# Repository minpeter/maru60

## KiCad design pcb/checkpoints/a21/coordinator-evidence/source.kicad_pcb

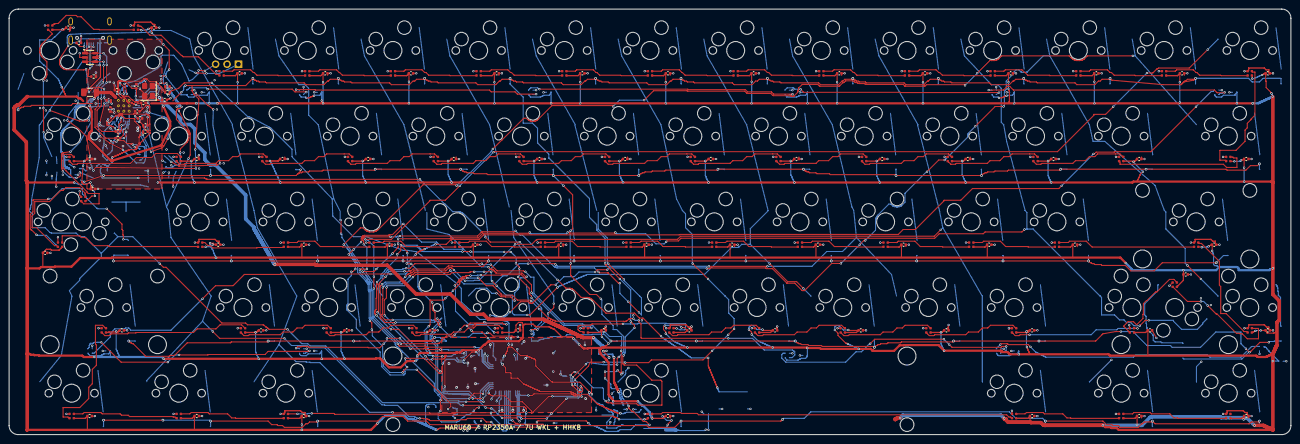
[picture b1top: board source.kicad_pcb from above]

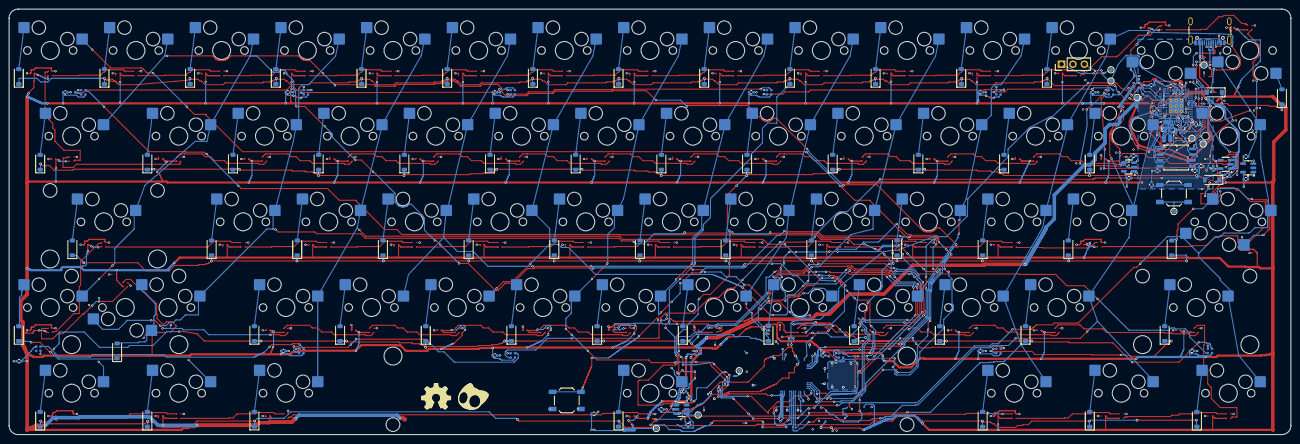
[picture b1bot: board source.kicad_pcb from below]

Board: 4 copper layers, 285.0 x 94.6 mm, 340 parts (192 on the bottom side), 193 nets.

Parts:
C100, C101: 1u 10V; C_0402_1005Metric
C102, C103: 4.7u 6.3V; C_0402_Official_R4_Wide
C104: 4.7u 6.3V; C_0402_1005Metric
C105, C108, C110, C111, C112, C113, C114, C115, C116, C117, C118, C122, C123, C199: 100n; C_0402_1005Metric
C106, C107: 15p C0G; C_0402_1005Metric
C109: 4.7u 6.3V X5R; C_0402_1005Metric
C120: 1u; C_0402_1005Metric
C121: 4.7u; C_0402_1005Metric
C200, C201, C202, C203, C204, C205, C206, C207, C208, C209, C210, C211, C212, C213, C214, C215, C216, C217, C218, C219, C220, C221, C222, C223, C224, C225, C226, C227, C228, C229, C230, C231, C232, C233, C234, C235, C236, C237, C238, C239, C240, C241, C242, C243, C244, C245, C246, C247, C248, C249, C250, C251, C252, C253, C254, C255, C256, C257, C258, C259, C260, C261, C262, C263, C264, C265, C266, C267, C268, C269, C270, C271, C272, C273: 100nF; C_0402_1005Metric
C274, C275: 100nF 10V X7R candidate; C_0402_1005Metric
D1, D2, D3, D4, D5, D6, D7, D8, D9, D10, D11, D12, D13, D14, D15, D16, D17, D18, D19, D20, D21, D22, D23, D24, D25, D26, D27, D28, D29, D30, D31, D32, D33, D34, D35, D36, D37, D38, D39, D40, D41, D42, D43, D44, D45, D46, D47, D48, D49, D50, D51, D52, D53, D54, D55, D56, D57, D58, D59, D60, D61, D62: 1N4148W; D_SOD-123
F1: 500mA hold candidate; Fuse_1206_3216Metric
J1: USB4105-GF-A (candidate); USB_C_Receptacle_GCT_USB4105-xx-A_16P_TopMnt_Horizontal
J2: SWD / GND / SWCLK; PinHeader_1x03_P2.54mm_Vertical
L1: 3.3uH AOTA-B201610S3R3-101-T; Abracon_AOTA_B201610S3R3_Official_R4
LED1, LED2, LED3, LED4, LED5, LED6, LED7, LED8, LED9, LED10, LED11, LED12, LED13, LED14, LED15, LED16, LED17, LED18, LED19, LED20, LED21, LED22, LED23, LED24, LED25, LED26, LED27, LED28, LED29, LED30, LED31, LED32, LED33, LED34, LED35, LED36, LED37, LED38, LED39, LED40, LED41, LED42, LED43, LED44, LED45, LED46, LED47, LED48, LED49, LED50, LED51, LED52, LED53, LED54, LED55, LED56, LED57, LED58, LED59, LED60, LED61, LED62, LED63, LED64, LED65, LED66, LED67, LED68, LED69, LED70, LED71, LED72, LED73, LED74, LED75, LED76: SK6805-EC15-001; LED_SK6805_EC15_001_Recommended_Candidate
LOGO1: OSHW + minpeter character — DRAFT; OSHW_then_Minpeter_H6_Gap1p5_Silk_DRAFT
R100, R101: 5.1k 1%; R_0402_1005Metric
R102, R103: 27; R_0402_1005Metric
R104: 33; R_0402_1005Metric
R105, R113, R114: 10k; R_0402_1005Metric
R106, R107, R108: 1k; R_0402_1005Metric
R109: 100k; R_0402_1005Metric
R110, R111: 330; R_0402_1005Metric
R112: 133k 1%; R_0402_1005Metric
STAB_RS1: (no value)
SW1: Esc; MX-Hotswap-1U
SW2: 1; MX-Hotswap-1U
SW3: 2; MX-Hotswap-1U
SW4: 3; MX-Hotswap-1U
SW5: 4; MX-Hotswap-1U
SW6: 5; MX-Hotswap-1U
SW7: 6; MX-Hotswap-1U
SW8: 7; MX-Hotswap-1U
SW9: 8; MX-Hotswap-1U
SW10: 9; MX-Hotswap-1U
SW11: 0; MX-Hotswap-1U
SW12: Minus; MX-Hotswap-1U
SW13: Equal; MX-Hotswap-1U
SW14: Backspace_L; MX-Hotswap-1U
SW15: Backspace_R; MX-Hotswap-1U
SW16: Tab; MX-Hotswap-1U
SW17: Q; MX-Hotswap-1U
SW18: W; MX-Hotswap-1U
SW19: E; MX-Hotswap-1U
SW20: R; MX-Hotswap-1U
SW21: T; MX-Hotswap-1U
SW22: Y; MX-Hotswap-1U
SW23: U; MX-Hotswap-1U
SW24: I; MX-Hotswap-1U
SW25: O; MX-Hotswap-1U
SW26: P; MX-Hotswap-1U
SW27: LeftBracket; MX-Hotswap-1U
SW28: RightBracket; MX-Hotswap-1U
SW29: Backslash; MX-Hotswap-1U
SW31: A; MX-Hotswap-1U
SW32: S; MX-Hotswap-1U
SW33: D; MX-Hotswap-1U
SW34: F; MX-Hotswap-1U
SW35: G; MX-Hotswap-1U
SW36: H; MX-Hotswap-1U
SW37: J; MX-Hotswap-1U
SW38: K; MX-Hotswap-1U
SW39: L; MX-Hotswap-1U
SW40: Semicolon; MX-Hotswap-1U
SW41: Quote; MX-Hotswap-1U
SW42: Enter; MX-Hotswap-2.25U-4L-NPTH
SW43: LeftShift; MX-Hotswap-2.25U-4L-NPTH
SW44: Z; MX-Hotswap-1U
SW45: X; MX-Hotswap-1U
SW46: C; MX-Hotswap-1U
SW47: V; MX-Hotswap-1U
SW48: B; MX-Hotswap-1U
SW49: N; MX-Hotswap-1U
SW50: M; MX-Hotswap-1U
SW51: Comma; MX-Hotswap-1U
SW52: Period; MX-Hotswap-1U
SW53: Slash; MX-Hotswap-1U
SW56: LCtrl; MX-Hotswap-1U
SW57: LMeta; MX-Hotswap-1U
SW58: LAlt; MX-Hotswap-1U
SW59: Space; MX-Hotswap-7U-4L-NPTH-StabRot180
SW60: RAlt; MX-Hotswap-1U
SW61: RMeta; MX-Hotswap-1U
SW62: RCtrl; MX-Hotswap-1U
SW100: BOOTSEL; SW_SPST_TL3342
SW101: RESET; SW_SPST_TL3342
SWCAP1: Caps_Options; MX_Study_Caps_Normal_or_Stepped
SWRS1: RShift_Options; MX_Study_RShift_2.75U_or_1.75U_1U
TP1: GND TEST; TestPoint_Pad_D1.0mm
TP2: VBUS TEST; TestPoint_Pad_D1.0mm
TP3: +5V TEST; TestPoint_Pad_D1.0mm
TP4: +3V3 TEST; TestPoint_Pad_D1.0mm
TP5: +1V1 TEST; TestPoint_Pad_D1.0mm
TP6: RUN TEST; TestPoint_Pad_D1.0mm
TP7: SWDIO TEST; TestPoint_Pad_D1.0mm
TP8: SWCLK TEST; TestPoint_Pad_D1.0mm
TP9: LED_FAULT_N TEST; TestPoint_Pad_D1.0mm
TP10: +5V_LED TEST; TestPoint_Pad_D1.0mm
U1: RP2350A (A4 required); RP2350A_QFN60_Official_R4
U2: AP2112K-3.3TRG1; SOT-23-5
U3: W25Q32JVSSIQ (4MiB); SOIC-8_5.3x5.3mm_P1.27mm
U4: USBLC6-2SC6; SOT-23-6
U5, U6: SN74LV1T125DBVR; SOT-23-5
U7: TPS2553DBVR-1; SOT-23-6
Y1: 12MHz ABM8-272-T3; Crystal_SMD_3225-4Pin_3.2x2.5mm

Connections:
+1V1: C103.1, C108.1, C109.1, C110.1, L1.1, TP5.1, U1.6, U1.23, U1.39, U1.50
+3V3: C101.1, C102.1, C105.1, C111.1, C112.1, C113.1, C114.1, C115.1, C116.1, C117.1, C118.1, C199.1, R104.1, R105.1, R113.1, TP4.1, U1.1, U1.11, U1.20, U1.30, U1.38, U1.44, U1.45, U1.49, U1.53, U1.54, U2.5, U3.8
+5V: C100.1, C120.1, F1.2, TP3.1, U2.1, U2.3, U7.1
+5V_LED: C121.1, C122.1, C123.1, C200.1, C201.1, C202.1, C203.1, C204.1, C205.1, C206.1, C207.1, C208.1, C209.1, C210.1, C211.1, C212.1, C213.1, C214.1, C215.1, C216.1, C217.1, C218.1, C219.1, C220.1, C221.1, C222.1, C223.1, C224.1, C225.1, C226.1, C227.1, C228.1, C229.1, C230.1, C231.1, C232.1, C233.1, C234.1, C235.1, C236.1, C237.1, C238.1, C239.1, C240.1, C241.1, C242.1, C243.1, C244.1, C245.1, C246.1, C247.1, C248.1, C249.1, C250.1, C251.1, C252.1, C253.1, C254.1, C255.1, C256.1, C257.1, C258.1, C259.1, C260.1, C261.1, C262.1, C263.1, C264.1, C265.1, C266.1, C267.1, C268.1, C269.1, C270.1, C271.1, C272.1, C273.1, C274.1, C275.1, LED1.2, LED2.2, LED3.2, LED4.2, LED5.2, LED6.2, LED7.2, LED8.2, LED9.2, LED10.2, LED11.2, LED12.2, LED13.2, LED14.2, LED15.2, LED16.2, LED17.2, LED18.2, LED19.2, LED20.2, LED21.2, LED22.2, LED23.2, LED24.2, LED25.2, LED26.2, LED27.2, LED28.2, LED29.2, LED30.2, LED31.2, LED32.2, LED33.2, LED34.2, LED35.2, LED36.2, LED37.2, LED38.2, LED39.2, LED40.2, LED41.2, LED42.2, LED43.2, LED44.2, LED45.2, LED46.2, LED47.2, LED48.2, LED49.2, LED50.2, LED51.2, LED52.2, LED53.2, LED54.2, LED55.2, LED56.2, LED57.2, LED58.2, LED59.2, LED60.2, LED61.2, LED62.2, LED63.2, LED64.2, LED65.2, LED66.2, LED67.2, LED68.2, LED69.2, LED70.2, LED71.2, LED72.2, LED73.2, LED74.2, LED75.2, LED76.2, R114.1, TP10.1, U5.5, U6.5, U7.6
BOOT_BUTTON: R106.2, SW100.1
CC1: J1.A5, R100.1
CC2: J1.B5, R101.1
COL0: SW1.1, SW16.1, SW43.1, SW56.1, SWCAP1.1, SWCAP1.3, U1.8
COL1: SW2.1, SW17.1, SW31.1, SW44.1, SW57.1, U1.9
COL2: SW3.1, SW18.1, SW32.1, SW45.1, SW58.1, U1.10
COL3: SW4.1, SW19.1, SW33.1, SW46.1, U1.12
COL4: SW5.1, SW20.1, SW34.1, SW47.1, U1.13
COL5: SW6.1, SW21.1, SW35.1, SW48.1, U1.42
COL6: SW7.1, SW22.1, SW36.1, SW49.1, SW59.1, U1.15
COL7: SW8.1, SW23.1, SW37.1, SW50.1, U1.16
COL8: SW9.1, SW24.1, SW38.1, SW51.1, U1.17
COL9: SW10.1, SW25.1, SW39.1, SW52.1, U1.18
COL10: SW11.1, SW26.1, SW40.1, SW53.1, SW60.1, U1.19
COL11: SW12.1, SW27.1, SW41.1, SW61.1, SWRS1.1, SWRS1.3, U1.27
COL12: SW13.1, SW28.1, SW42.1, SW62.1, SWRS1.5, U1.28
COL13: SW14.1, SW29.1, U1.29
COL14: SW15.1, U1.31
GND: C100.2, C101.2, C102.2, C103.2, C104.2, C105.2, C106.2, C107.2, C108.2, C109.2, C110.2, C111.2, C112.2, C113.2, C114.2, C115.2, C116.2, C117.2, C118.2, C120.2, C121.2, C122.2, C123.2, C199.2, C200.2, C201.2, C202.2, C203.2, C204.2, C205.2, C206.2, C207.2, C208.2, C209.2, C210.2, C211.2, C212.2, C213.2, C214.2, C215.2, C216.2, C217.2, C218.2, C219.2, C220.2, C221.2, C222.2, C223.2, C224.2, C225.2, C226.2, C227.2, C228.2, C229.2, C230.2, C231.2, C232.2, C233.2, C234.2, C235.2, C236.2, C237.2, C238.2, C239.2, C240.2, C241.2, C242.2, C243.2, C244.2, C245.2, C246.2, C247.2, C248.2, C249.2, C250.2, C251.2, C252.2, C253.2, C254.2, C255.2, C256.2, C257.2, C258.2, C259.2, C260.2, C261.2, C262.2, C263.2, C264.2, C265.2, C266.2, C267.2, C268.2, C269.2, C270.2, C271.2, C272.2, C273.2, C274.2, C275.2, J1.A1, J1.A12, J1.B1, J1.B12, J1.S1, J2.2, LED1.4, LED2.4, LED3.4, LED4.4, LED5.4, LED6.4, LED7.4, LED8.4, LED9.4, LED10.4, LED11.4, LED12.4, LED13.4, LED14.4, LED15.4, LED16.4, LED17.4, LED18.4, LED19.4, LED20.4, LED21.4, LED22.4, LED23.4, LED24.4, LED25.4, LED26.4, LED27.4, LED28.4, LED29.4, LED30.4, LED31.4, LED32.4, LED33.4, LED34.4, LED35.4, LED36.4, LED37.4, LED38.4, LED39.4, LED40.4, LED41.4, LED42.4, LED43.4, LED44.4, LED45.4, LED46.4, LED47.4, LED48.4, LED49.4, LED50.4, LED51.4, LED52.4, LED53.4, LED54.4, LED55.4, LED56.4, LED57.4, LED58.4, LED59.4, LED60.4, LED61.4, LED62.4, LED63.4, LED64.4, LED65.4, LED66.4, LED67.4, LED68.4, LED69.4, LED70.4, LED71.4, LED72.4, LED73.4, LED74.4, LED75.4, LED76.4, R100.2, R101.2, R107.2, R109.2, R112.2, R114.2, SW100.2, TP1.1, U1.47, U1.61, U2.2, U3.4, U4.2, U5.1, U5.3, U6.1, U6.3, U7.2, Y1.2, Y1.4
KEY_1: D1.2, SW1.2
KEY_2: D2.2, SW2.2
KEY_3: D3.2, SW3.2
KEY_4: D4.2, SW4.2
KEY_5: D5.2, SW5.2
KEY_6: D6.2, SW6.2
KEY_7: D7.2, SW7.2
KEY_8: D8.2, SW8.2
KEY_9: D9.2, SW9.2
KEY_10: D10.2, SW10.2
KEY_11: D11.2, SW11.2
KEY_12: D12.2, SW12.2
KEY_13: D13.2, SW13.2
KEY_14: D14.2, SW14.2
KEY_15: D15.2, SW15.2
KEY_16: D16.2, SW16.2
KEY_17: D17.2, SW17.2
KEY_18: D18.2, SW18.2
KEY_19: D19.2, SW19.2
KEY_20: D20.2, SW20.2
KEY_21: D21.2, SW21.2
KEY_22: D22.2, SW22.2
KEY_23: D23.2, SW23.2
KEY_24: D24.2, SW24.2
KEY_25: D25.2, SW25.2
KEY_26: D26.2, SW26.2
KEY_27: D27.2, SW27.2
KEY_28: D28.2, SW28.2
KEY_29: D29.2, SW29.2
KEY_30: D30.2, SWCAP1.2, SWCAP1.4
KEY_31: D31.2, SW31.2
KEY_32: D32.2, SW32.2
KEY_33: D33.2, SW33.2
KEY_34: D34.2, SW34.2
KEY_35: D35.2, SW35.2
KEY_36: D36.2, SW36.2
KEY_37: D37.2, SW37.2
KEY_38: D38.2, SW38.2
KEY_39: D39.2, SW39.2
KEY_40: D40.2, SW40.2
KEY_41: D41.2, SW41.2
KEY_42: D42.2, SW42.2
KEY_43: D43.2, SW43.2
KEY_44: D44.2, SW44.2
KEY_45: D45.2, SW45.2
KEY_46: D46.2, SW46.2
KEY_47: D47.2, SW47.2
KEY_48: D48.2, SW48.2
KEY_49: D49.2, SW49.2
KEY_50: D50.2, SW50.2
KEY_51: D51.2, SW51.2
KEY_52: D52.2, SW52.2
KEY_53: D53.2, SW53.2
KEY_54: D54.2, SWRS1.2, SWRS1.4
KEY_55: D55.2, SWRS1.6
KEY_56: D56.2, SW56.2
KEY_57: D57.2, SW57.2
KEY_58: D58.2, SW58.2
KEY_59: D59.2, SW59.2
KEY_60: D60.2, SW60.2
KEY_61: D61.2, SW61.2
KEY_62: D62.2, SW62.2
KEY_RGB: U1.32, U5.2
KEY_RGB_5V: LED1.1, R110.2
KEY_RGB_5V_BUF: R110.1, U5.4
KEY_RGB_CHAIN_1: LED1.3, LED2.1
KEY_RGB_CHAIN_2: LED2.3, LED3.1
KEY_RGB_CHAIN_3: LED3.3, LED4.1
KEY_RGB_CHAIN_4: LED4.3, LED5.1
KEY_RGB_CHAIN_5: LED5.3, LED6.1
KEY_RGB_CHAIN_6: LED6.3, LED7.1
KEY_RGB_CHAIN_7: LED7.3, LED8.1
KEY_RGB_CHAIN_8: LED8.3, LED9.1
KEY_RGB_CHAIN_9: LED9.3, LED10.1
KEY_RGB_CHAIN_10: LED10.3, LED11.1
KEY_RGB_CHAIN_11: LED11.3, LED12.1
KEY_RGB_CHAIN_12: LED12.3, LED13.1
KEY_RGB_CHAIN_13: LED13.3, LED14.1
KEY_RGB_CHAIN_14: LED14.3, LED15.1
KEY_RGB_CHAIN_15: LED15.3, LED29.1
KEY_RGB_CHAIN_16: LED28.1, LED29.3
KEY_RGB_CHAIN_17: LED27.1, LED28.3
KEY_RGB_CHAIN_18: LED26.1, LED27.3
KEY_RGB_CHAIN_19: LED25.1, LED26.3
KEY_RGB_CHAIN_20: LED24.1, LED25.3
KEY_RGB_CHAIN_21: LED23.1, LED24.3
KEY_RGB_CHAIN_22: LED22.1, LED23.3
KEY_RGB_CHAIN_23: LED21.1, LED22.3
KEY_RGB_CHAIN_24: LED20.1, LED21.3
KEY_RGB_CHAIN_25: LED19.1, LED20.3
KEY_RGB_CHAIN_26: LED18.1, LED19.3
KEY_RGB_CHAIN_27: LED17.1, LED18.3
KEY_RGB_CHAIN_28: LED16.1, LED17.3
KEY_RGB_CHAIN_29: LED16.3, LED30.1
KEY_RGB_CHAIN_30: LED30.3, LED75.1
KEY_RGB_CHAIN_31: LED31.1, LED75.3
KEY_RGB_CHAIN_32: LED31.3, LED32.1
KEY_RGB_CHAIN_33: LED32.3, LED33.1
KEY_RGB_CHAIN_34: LED33.3, LED34.1
KEY_RGB_CHAIN_35: LED34.3, LED35.1
KEY_RGB_CHAIN_36: LED35.3, LED36.1
KEY_RGB_CHAIN_37: LED36.3, LED37.1
KEY_RGB_CHAIN_38: LED37.3, LED38.1
KEY_RGB_CHAIN_39: LED38.3, LED39.1
KEY_RGB_CHAIN_40: LED39.3, LED40.1
KEY_RGB_CHAIN_41: LED40.3, LED41.1
KEY_RGB_CHAIN_42: LED41.3, LED42.1
KEY_RGB_CHAIN_43: LED42.3, LED55.1
KEY_RGB_CHAIN_44: LED55.3, LED76.1
KEY_RGB_CHAIN_45: LED54.1, LED76.3
KEY_RGB_CHAIN_46: LED53.1, LED54.3
KEY_RGB_CHAIN_47: LED52.1, LED53.3
KEY_RGB_CHAIN_48: LED51.1, LED52.3
KEY_RGB_CHAIN_49: LED50.1, LED51.3
KEY_RGB_CHAIN_50: LED49.1, LED50.3
KEY_RGB_CHAIN_51: LED48.1, LED49.3
KEY_RGB_CHAIN_52: LED47.1, LED48.3
KEY_RGB_CHAIN_53: LED46.1, LED47.3
KEY_RGB_CHAIN_54: LED45.1, LED46.3
KEY_RGB_CHAIN_55: LED44.1, LED45.3
KEY_RGB_CHAIN_56: LED43.1, LED44.3
KEY_RGB_CHAIN_57: LED43.3, LED56.1
KEY_RGB_CHAIN_58: LED56.3, LED57.1
KEY_RGB_CHAIN_59: LED57.3, LED58.1
KEY_RGB_CHAIN_60: LED58.3, LED59.1
KEY_RGB_CHAIN_61: LED59.3, LED60.1
KEY_RGB_CHAIN_62: LED60.3, LED61.1
KEY_RGB_CHAIN_63: LED61.3, LED62.1
LED_ENABLE: R109.1, U1.34, U7.3
LED_FAULT_N: R113.2, TP9.1, U1.35, U7.4
LED_ILIM: R112.1, U7.5
QSPI_SCLK: U1.56, U3.6
QSPI_SD0: U1.57, U3.5
QSPI_SD1: U1.59, U3.2
QSPI_SD2: U1.58, U3.3
QSPI_SD3: U1.55, U3.7
QSPI_SS: R105.2, R106.1, U1.60, U3.1
RESET_GND: R107.1, SW101.2
ROW0: D1.1, D2.1, D3.1, D4.1, D5.1, D6.1, D7.1, D8.1, D9.1, D10.1, D11.1, D12.1, D13.1, D14.1, D15.1, U1.2
ROW1: D16.1, D17.1, D18.1, D19.1, D20.1, D21.1, D22.1, D23.1, D24.1, D25.1, D26.1, D27.1, D28.1, D29.1, U1.3
ROW2: D30.1, D31.1, D32.1, D33.1, D34.1, D35.1, D36.1, D37.1, D38.1, D39.1, D40.1, D41.1, D42.1, U1.4
ROW3: D43.1, D44.1, D45.1, D46.1, D47.1, D48.1, D49.1, D50.1, D51.1, D52.1, D53.1, D54.1, D55.1, U1.43
ROW4: D56.1, D57.1, D58.1, D59.1, D60.1, D61.1, D62.1, U1.7
RUN: SW101.1, TP6.1, U1.26
SWCLK: J2.3, TP8.1, U1.24
SWDIO: J2.1, TP7.1, U1.25
UG_LED_1: LED63.3, LED64.1
UG_LED_2: LED64.3, LED65.1
UG_LED_3: LED65.3, LED66.1
UG_LED_4: LED66.3, LED67.1
UG_LED_5: LED67.3, LED68.1
UG_LED_6: LED68.3, LED69.1
UG_LED_7: LED69.3, LED70.1
UG_LED_8: LED70.3, LED71.1
UG_LED_9: LED71.3, LED72.1
UG_LED_10: LED72.3, LED73.1
UG_LED_11: LED73.3, LED74.1
UNDERGLOW: U1.33, U6.2
UNDERGLOW_5V: LED63.1, R111.2
UNDERGLOW_5V_BUF: R111.1, U6.4
USB_DM: R103.2, U1.51
USB_DM_CONN: J1.A7, J1.B7, R103.1, U4.3, U4.4
USB_DP: R102.2, U1.52
USB_DP_CONN: J1.A6, J1.B6, R102.1, U4.1, U4.6
VBUS: F1.1, J1.A4, J1.A9, J1.B4, J1.B9, TP2.1, U4.5
VREG_AVDD: C104.1, R104.2, U1.46
VREG_LX: L1.2, U1.48
XIN: C106.1, U1.21, Y1.1
XOUT: R108.2, U1.22
XTAL_OUT: C107.1, R108.1, Y1.3

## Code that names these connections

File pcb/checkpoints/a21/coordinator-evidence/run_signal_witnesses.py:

from pathlib import Path
import json,hashlib,subprocess,os
D=Path(__file__).parent;O=D/'signal-source-gates';O.mkdir(exist_ok=False);B=D/'candidate.kicad_pcb';C=Path('/workspace/shared/maru60-kicad-linux/pcb/tools/studies/experiment_a_power_witness.py');sha=lambda p:hashlib.sha256(p.read_bytes()).hexdigest();inputs=[B,B.with_suffix('.kicad_pro'),C];base={str(p):sha(p)for p in inputs};rows=[];env=os.environ.copy();env['KICAD_CONFIG_HOME']='/tmp/maru-kicad-config'
for name,net,ref,pin in [('XIN','XIN','U1','21'),('XOUT','XOUT','U1','22'),('XTAL','XTAL_OUT','R108','1'),('UNDERGLOW','UNDERGLOW','U1','33'),('FAULT','LED_FAULT_N','U7','4'),('ENABLE','LED_ENABLE','U1','34'),('COL1','COL1','U1','9')]:
 assert {str(p):sha(p)for p in inputs}==base
 with (O/(name+'.log')).open('w')as log:r=subprocess.run(['/usr/bin/python3',str(C),str(B),str(O/(name+'.json')),net,ref,pin],stdout=log,stderr=subprocess.STDOUT,env=env)
 assert r.returncode==0 and {str(p):sha(p)for p in inputs}==base
 j=json.load(open(O/(name+'.json')));assert not j['unreached_components'];rows.append({'name':name,'source_pad':[ref,pin],'unreached_components':0,'report_sha256':sha(O/(name+'.json'))})
(O/'BOUND-SIGNAL-RESULT.json').write_text(json.dumps({'status':'COMPLETED','bound_inputs':base,'results':rows},indent=2));print('seven source signal witnesses PASS')
